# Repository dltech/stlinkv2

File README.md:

# stlinkv2
ST-link V2 schematic and PCB in kiCAD with initial firmware through UART.
1. PCB templates for prototyping at home are photoresist.svg and lut.svg, also you can convert PCB to any of appropriate formats using KiCAD.
2. As you seen above, for this solution you do not need any other st-link, you need only usb-uart adapter.
3. When you got a board, pull up pin 44 BOOT0 to Vbus by R4 resistor, so after power connect the MCU starts up from the UART bootloader.
4. Power up board by USB and connect it to your PC through UART by RX and TX pads.
5. Write dummy firmware from STLinkV2_bin.zip using the flasher utility (ST UM0462).
6. Return pull down resistor to pin 44 BOOT0 (change location of 10-100K resistor from R4 to R5 place).
7. Then connect it to USB and write the firmware from ST using upgrade utility stlink-V2.J21.S4.zip. Now you got a working st-link clone.

On the linux using the Virtualbox software this method is working too.

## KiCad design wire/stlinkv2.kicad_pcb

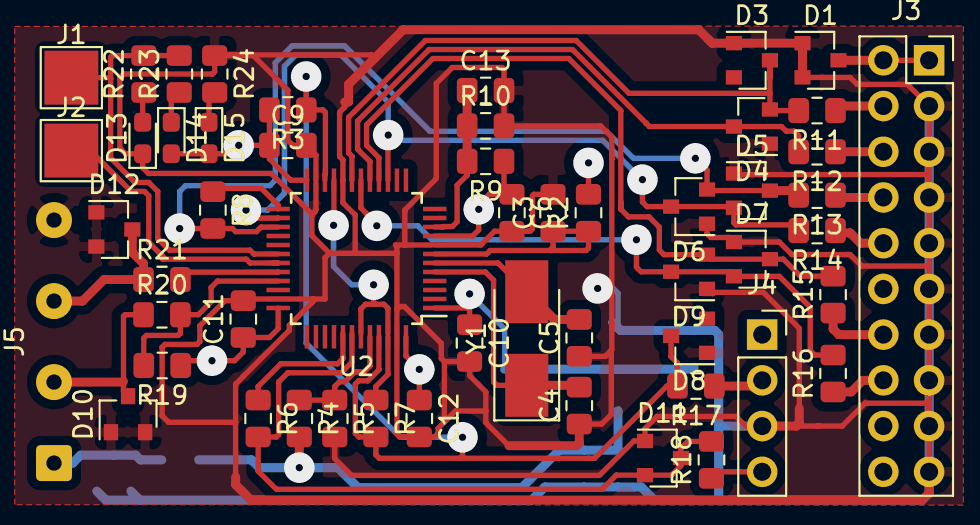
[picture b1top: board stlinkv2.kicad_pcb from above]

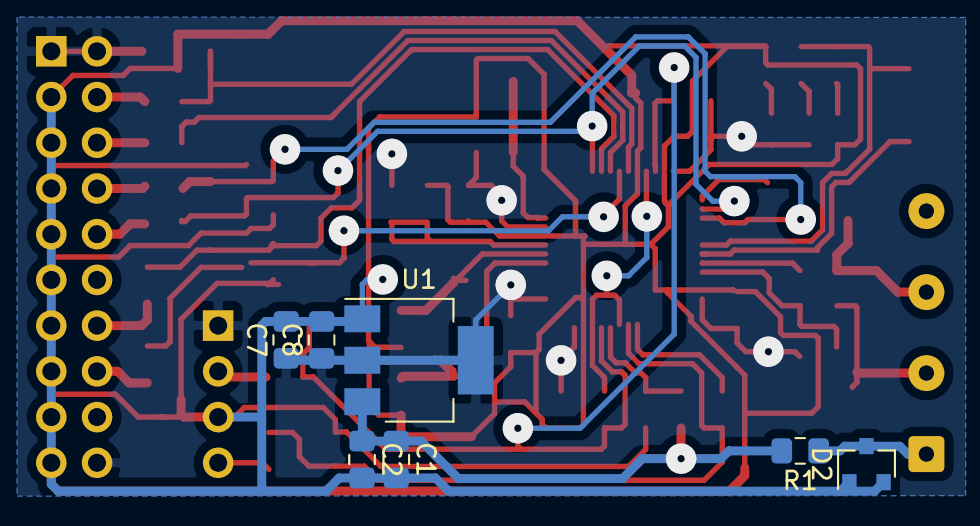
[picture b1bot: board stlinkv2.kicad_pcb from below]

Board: 2 copper layers, 60 parts (7 on the bottom side), 37 nets.

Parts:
C1, C7: 10; C_0805_2012Metric_Pad1.15x1.40mm_HandSolder
C2, C3, C6, C8, C9, C10, C11, C12, C13: 0.1; C_0805_2012Metric_Pad1.15x1.40mm_HandSolder
C4, C5: 22p; C_0805_2012Metric_Pad1.15x1.40mm_HandSolder
D1, D2, D3, D4, D5, D6, D7, D8, D9, D10, D11, D12: BZX84-C5V1; D_SOT-23_ANK
D13, D15: red; LED_0603_1608Metric_Pad1.05x0.95mm_HandSolder
D14: green; LED_0603_1608Metric_Pad1.05x0.95mm_HandSolder
J1: TX; TestPoint_Pad_3.0x3.0mm
J2: RX; TestPoint_Pad_3.0x3.0mm
J3: JTAG; PinSocket_2x10_P2.54mm_Vertical
J4: SWIMM; PinSocket_1x04_P2.54mm_Vertical
J5: Conn_01x04; SolderWire-0.25sqmm_1x04_P4.5mm_D0.65mm_OD2mm
R1: 10; R_0805_2012Metric_Pad1.15x1.40mm_HandSolder
R2, R4, R5, R9, R10, R19: 100k; R_0805_2012Metric_Pad1.15x1.40mm_HandSolder
R3: 680; R_0805_2012Metric_Pad1.15x1.40mm_HandSolder
R6, R7, R8: 220; R_0805_2012Metric_Pad1.15x1.40mm_HandSolder
R11, R12, R13, R14, R15, R16, R17, R18, R20, R21: 75; R_0805_2012Metric_Pad1.15x1.40mm_HandSolder
R22, R23, R24: 100; R_0805_2012Metric_Pad1.15x1.40mm_HandSolder
U1: AZ1117-3.3; SOT-223-3_TabPin2
U2: STM32F103C8Tx; TQFP-48_7x7mm_P0.5mm
Y1: 8M; Crystal_SMD_5032-2Pin_5.0x3.2mm_HandSoldering

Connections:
+3V3: C6.1, C7.1, C8.1, C9.1, C10.1, C11.1, C12.1, D1.1, D14.2, D15.2, J3.1, J3.2, J3.19, J4.1, R2.2, R3.2, R9.1, R19.1, U1.2, U2.1, U2.9, U2.24, U2.36, U2.48
/LED: J1.1, R22.2, R23.2, U2.30
/NRST: D9.1, R16.2, U2.18
/SWIMM_DATA: D8.1, R3.1, R7.2, R17.2, U2.22, U2.45
/SWIMM_RST: D11.1, R6.2, R18.2, U2.42
/TCK_SWCLK: D6.1, R14.2, U2.15, U2.26
/TDI: D4.1, R12.2, U2.17
/TDO_SWO: D7.1, R15.2, U2.16
/TMS_SWDIO: D5.1, R8.2, R13.2, U2.27
/TRST: D3.1, R11.2, U2.19
/USBDM: R21.2, U2.32
/USBDP: R19.2, R20.2, U2.33
GND: C1.2, C2.2, C3.2, C4.1, C5.1, C6.2, C7.2, C8.2, C9.2, C10.2, C11.2, C12.2, C13.2, D1.2, D2.2, D3.2, D4.2, D5.2, D6.2, D7.2, D8.2, D9.2, D10.2, D11.2, D12.2, D13.1, J3.4, J3.6, J3.8, J3.10, J3.12, J3.14, J3.16, J3.18, J3.20, J4.3, J5.4, R5.2, R10.2, R24.1, U1.1, U2.8, U2.20, U2.23, U2.35, U2.47
unnamed: C3.1, R2.1, U2.7
unnamed: C4.2, U2.5, Y1.1
unnamed: C5.2, U2.6, Y1.2
unnamed: C13.1, R9.2, R10.1, U2.10
unnamed: D2.1, J5.1, R1.1
unnamed: D10.1, J5.2, R20.1
unnamed: D12.1, J5.3, R21.1
unnamed: D13.2, R22.1
unnamed: D14.1, R23.1
unnamed: D15.1, R24.2
unnamed: J2.1, U2.31
unnamed: J3.3, R11.1
unnamed: J3.5, R12.1
unnamed: J3.7, R13.1
unnamed: J3.9, R14.1
unnamed: J3.13, R15.1
unnamed: J3.15, R16.1
unnamed: J4.2, R17.1
unnamed: J4.4, R18.1
unnamed: R4.1, R5.1, U2.44
unnamed: R6.1, U2.41
unnamed: R7.1, U2.21, U2.43, U2.46
unnamed: R8.1, U2.25
VBUS: C1.1, C2.1, R1.2, R4.2, U1.3

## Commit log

2020-07-26 not tested but complete
2020-08-13 добавил светодиоды, проверю без них
2020-08-13 micro usb
2020-08-30 tested
2021-07-05 components
2021-07-16 pinouts
